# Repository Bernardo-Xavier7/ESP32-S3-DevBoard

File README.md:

# ESP32-S3 DevBoard
 ESP32 S3 DevBoard the size of a standard arduino nano.

## License 

This project uses a multi-licensing model to cover hardware, software, and documentation:

* **Hardware (Schematics, PCBs, CAD):** Licensed under [CERN-OHL-S-2.0](https://spdx.org)
* **Software & Firmware (Code):** Licensed under [GPL-3.0](https://spdx.org)
* **Documentation (Guides, Manuals):** Licensed under [CC-BY-SA-4.0](https://creativecommons.org)

For more information, please see the full [LICENSE](LICENSE) file in the root of this repository.

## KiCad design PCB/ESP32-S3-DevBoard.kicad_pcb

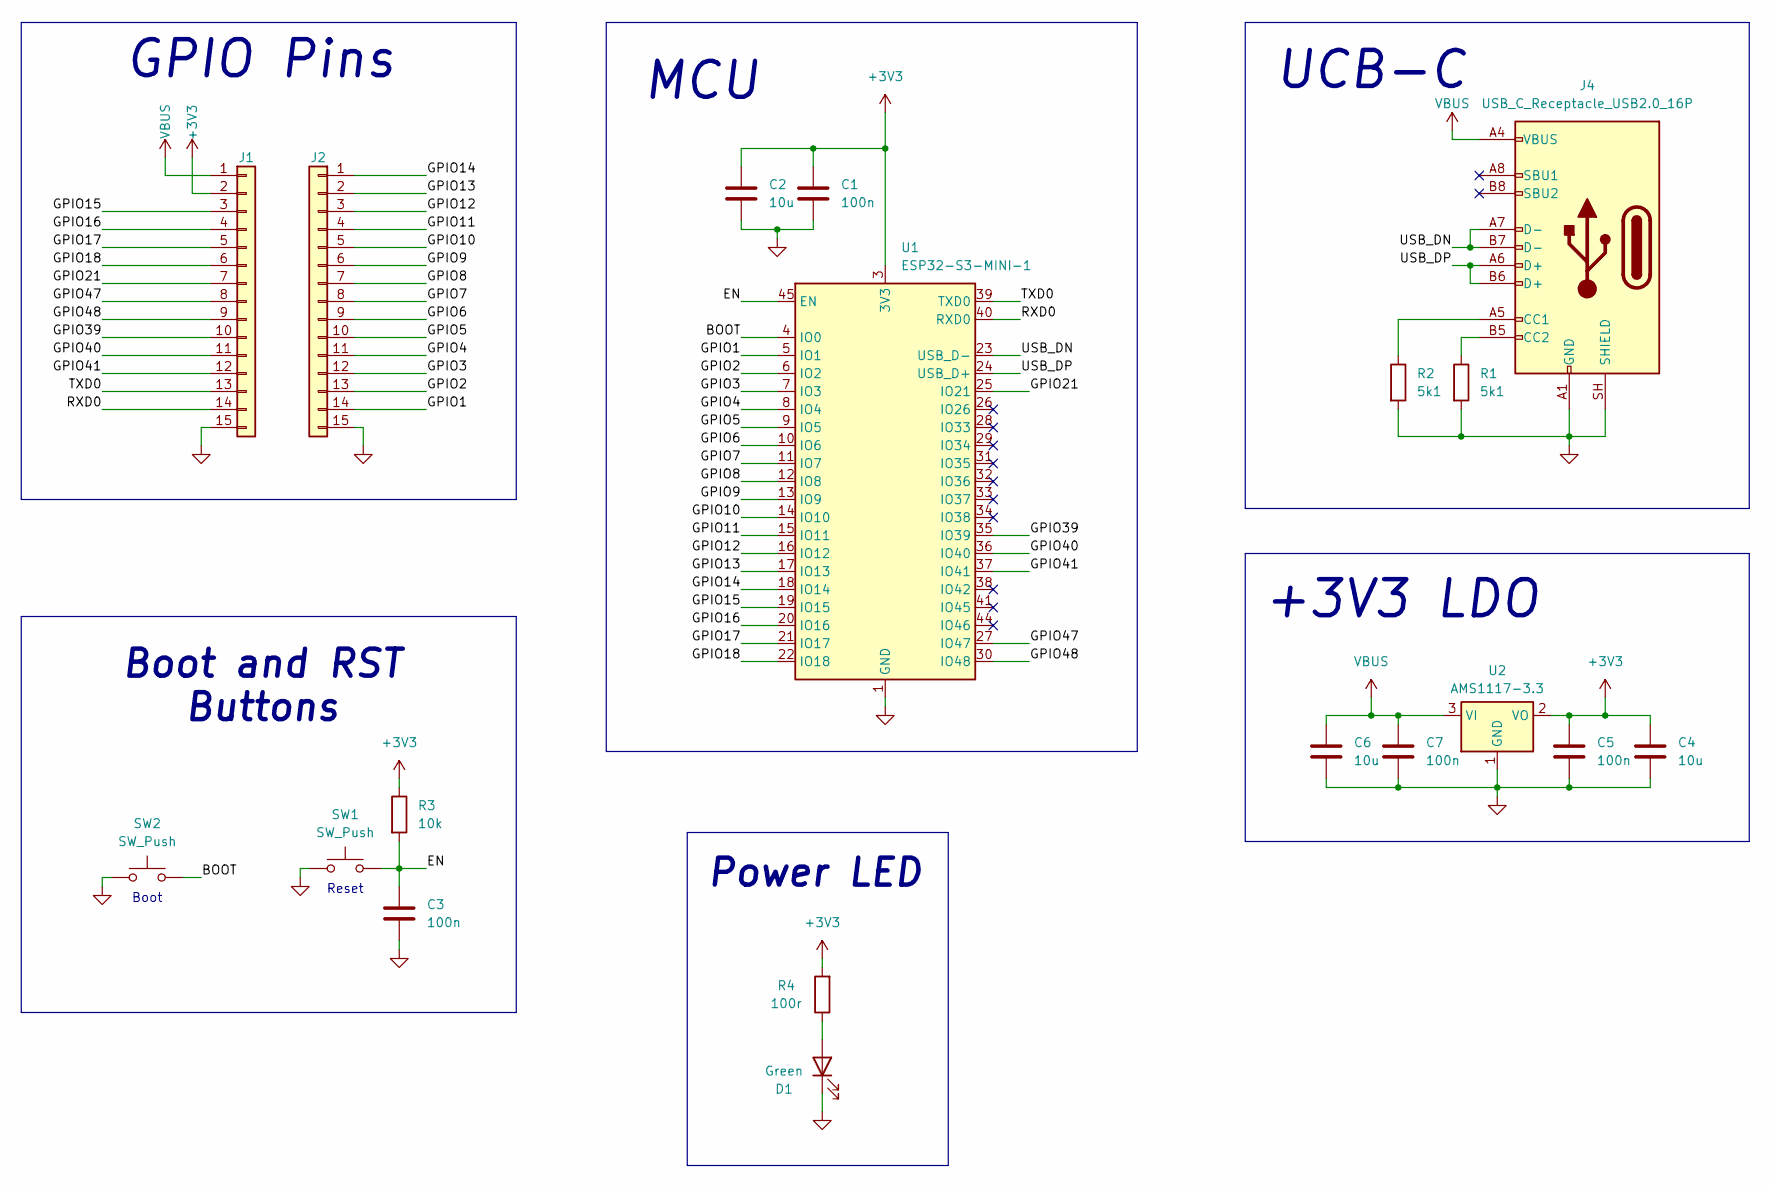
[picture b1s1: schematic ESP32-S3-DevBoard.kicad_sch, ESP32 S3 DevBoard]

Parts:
C1, C3, C5, C7: 100n; C_0603_1608Metric
C2, C4, C6: 10u; C_0603_1608Metric
D1: Green; LED_0603_1608Metric
J1: Analog; PinHeader_1x15_P2.54mm_Vertical
J2: Digital; PinHeader_1x15_P2.54mm_Vertical
J4: USB_C_Receptacle_USB2.0_16P; USB_C_Receptacle_G-Switch_GT-USB-7010ASV
R1, R2: 5k1; R_0603_1608Metric
R3: 10k; R_0603_1608Metric
R4: 100r; R_0603_1608Metric
SW1, SW2: SW_Push; SW_SPST_PTS810
U1: ESP32-S3-MINI-1; ESP32-S2-MINI-1
U2: AMS1117-3.3; SOT-223-3_TabPin2

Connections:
+3V3: C1.1, C2.1, C4.1, C5.1, J1.2, R3.1, R4.2, U1.3 (3V3), U2.2 (VO)
/BOOT: SW2.2, U1.4 (IO0)
/EN: C3.1, R3.2, SW1.2, U1.45 (EN)
/GPIO1: J2.14, U1.5 (IO1)
/GPIO2: J2.13, U1.6 (IO2)
/GPIO3: J2.12, U1.7 (IO3)
/GPIO4: J2.11, U1.8 (IO4)
/GPIO5: J2.10, U1.9 (IO5)
/GPIO6: J2.9, U1.10 (IO6)
/GPIO7: J2.8, U1.11 (IO7)
/GPIO8: J2.7, U1.12 (IO8)
/GPIO9: J2.6, U1.13 (IO9)
/GPIO10: J2.5, U1.14 (IO10)
/GPIO11: J2.4, U1.15 (IO11)
/GPIO12: J2.3, U1.16 (IO12)
/GPIO13: J2.2, U1.17 (IO13)
/GPIO14: J2.1, U1.18 (IO14)
/GPIO15: J1.3, U1.19 (IO15)
/GPIO16: J1.4, U1.20 (IO16)
/GPIO17: J1.5, U1.21 (IO17)
/GPIO18: J1.6, U1.22 (IO18)
/GPIO21: J1.7, U1.25 (IO21)
/GPIO39: J1.10, U1.35 (IO39)
/GPIO40: J1.11, U1.36 (IO40)
/GPIO41: J1.12, U1.37 (IO41)
/GPIO47: J1.8, U1.27 (IO47)
/GPIO48: J1.9, U1.30 (IO48)
/RXD0: J1.14, U1.40 (RXD0)
/TXD0: J1.13, U1.39 (TXD0)
/USB_DN: J4.A7 (D-), J4.B7 (D-), U1.23 (USB_D-)
/USB_DP: J4.A6 (D+), J4.B6 (D+), U1.24 (USB_D+)
GND: C1.2, C2.2, C3.2, C4.2, C5.2, C6.2, C7.2, D1.1 (K), J1.15, J2.15, J4.A1 (GND), J4.A12 (GND), J4.B1 (GND), J4.B12 (GND), J4.SH (SHIELD), R1.2, R2.2, SW1.1, SW2.1, U1.1 (GND), U1.2 (GND), U1.42 (GND), U1.43 (GND), U1.46 (GND), U1.47 (GND), U1.48 (GND), U1.49 (GND), U1.50 (GND), U1.51 (GND), U1.52 (GND), U1.53 (GND), U1.54 (GND), U1.55 (GND), U1.56 (GND), U1.57 (GND), U1.58 (GND), U1.59 (GND), U1.60 (GND), U1.61 (GND), U1.62 (GND), U1.63 (GND), U1.64 (GND), U1.65 (GND), U2.1 (GND)
unnamed: D1.2 (A), R4.1
unnamed: J4.A5 (CC1), R2.1
unnamed: J4.B5 (CC2), R1.1
VBUS: C6.1, C7.1, J1.1, J4.A4 (VBUS), J4.A9 (VBUS), J4.B4 (VBUS), J4.B9 (VBUS), U2.3 (VI)

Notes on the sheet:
+3V3 LDO
UCB-C
GPIO Pins
MCU
Reset
Boot
Boot and RST Buttons
Power LED

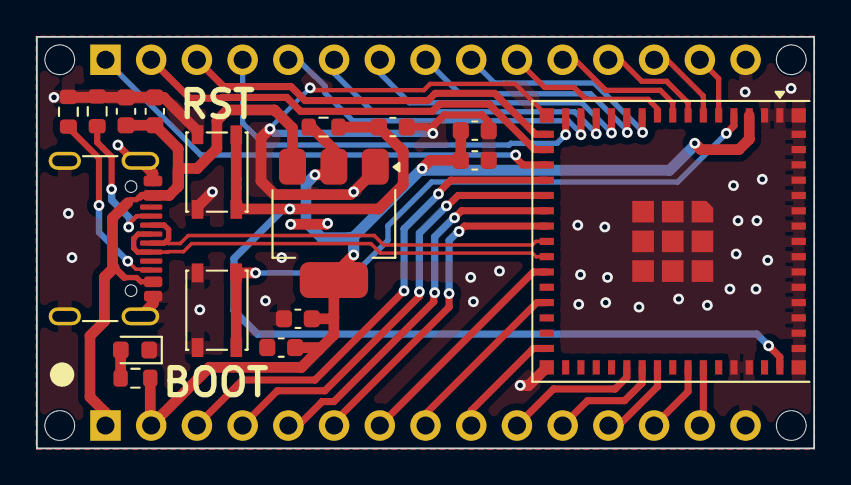
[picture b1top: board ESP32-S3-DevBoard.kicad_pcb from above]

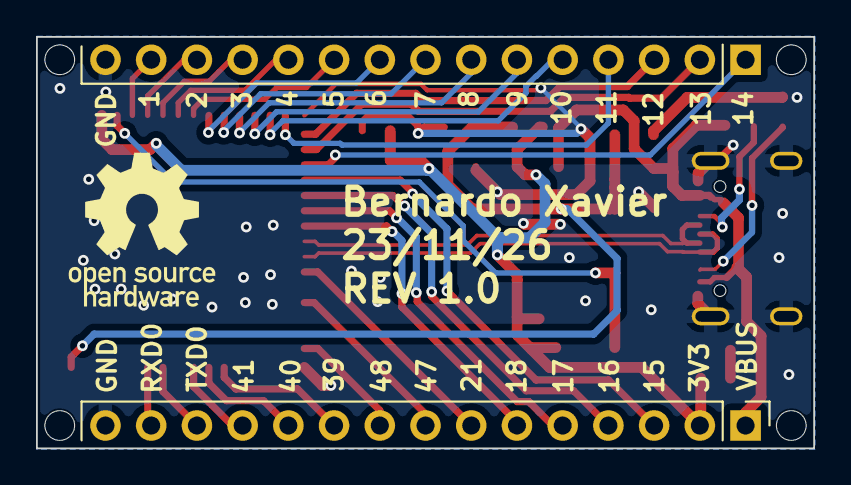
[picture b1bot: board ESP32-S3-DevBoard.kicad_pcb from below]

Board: 2 copper layers, 43.2 x 22.9 mm, 23 parts (2 on the bottom side), 36 nets.

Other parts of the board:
MH1, MH2, MH3, MH4: MountingHole_65mil
